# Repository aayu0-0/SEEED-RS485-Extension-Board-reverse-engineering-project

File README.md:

# Seeed Studio RS485 Extension Board — Reverse Engineering

A reverse-engineering and PCB recreation project of the **Seeed Studio RS485 Extension Board**.

The objective of this project is to understand the original board's electrical architecture, reproduce its schematic and PCB layout in KiCad, and generate a fabrication-ready design.

---

## 📌 Project Overview

This project involves analyzing the original Seeed Studio RS485 Extension Board and recreating its:

- Electrical schematic
- Power supply architecture
- RS485 communication interface
- Protection circuitry
- PCB layout
- Component footprints
- Manufacturing files

The recreated design is developed entirely in **KiCad**.

---

## 🎯 Objectives

- Reverse engineer the original RS485 extension board
- Understand the power and communication architecture
- Recreate the schematic in KiCad
- Select appropriate components and footprints
- Recreate the PCB layout
- Verify electrical connections and design rules
- Generate Gerber and drill files for PCB fabrication

---

## 🔧 Hardware

### Main Interfaces

- RS485 communication interface
- External power input
- Microcontroller/interface connection
- Protection circuitry

### Design Considerations

The design includes consideration for:

- RS485 differential signalling
- 120 Ω termination
- Fail-safe biasing
- Power regulation
- Reverse-polarity / transient protection
- Proper PCB grounding
- Controlled differential routing

---

## 🖥️ Software & Tools

| Tool | Purpose |
|------|---------|
| **KiCad** | Schematic and PCB design |
| **Git** | Version control |
| **GitHub** | Project hosting |
| **Datasheets** | Component verification |

---

## 📁 Repository Structure

```text
.
├── Home_Automation_v1.kicad_pro
├── Home_Automation_v1.kicad_sch
├── Home_Automation_v1.kicad_pcb
│
├── Home_Automation_v1.pretty/
│   └── Custom footprints
│
├── Final_Files/
│   ├── Gerber files
│   ├── Drill files
│   └── Gerber job file
│
└── README.md

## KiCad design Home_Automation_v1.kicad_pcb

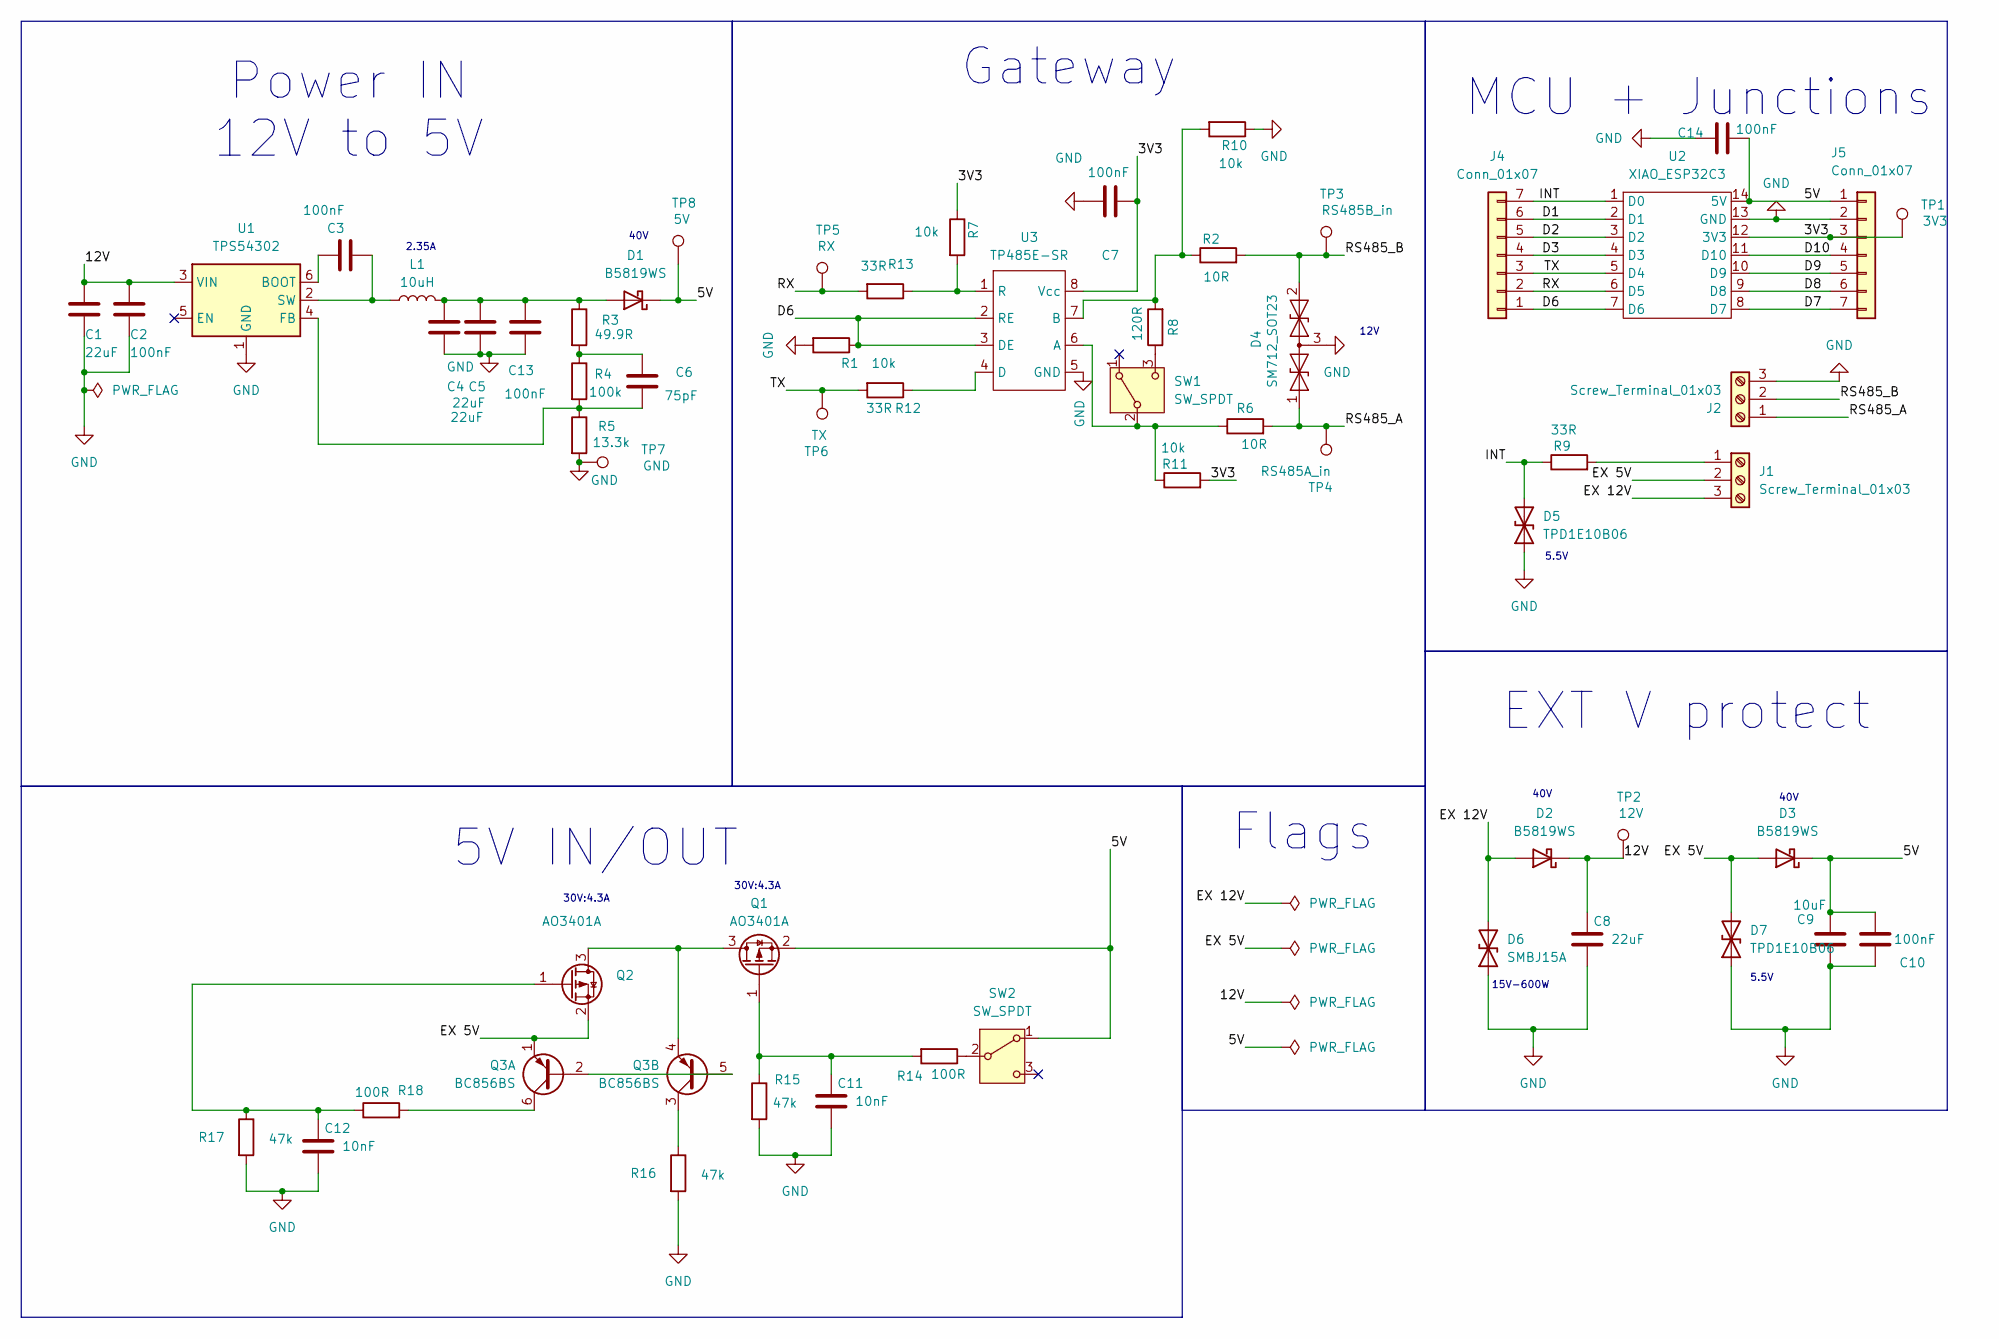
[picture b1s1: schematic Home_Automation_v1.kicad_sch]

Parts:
C1, C4, C5, C8: 22uF; C_0805_2012Metric
C2, C3, C7, C10, C13, C14: 100nF; C_0603_1608Metric
C6: 75pF; C_0603_1608Metric
C9: 10uF; C_0603_1608Metric
C11, C12: 10nF; C_0603_1608Metric
D1, D2, D3: B5819WS; D_SOD-323
D4: SM712_SOT23; SOT-23
D5, D7: TPD1E10B06; Texas_DPY0002A_0.6x1mm_P0.65mm
D6: SMBJ15A; D_SMB
J1, J2: Screw_Terminal_01x03; TerminalBlock_bornier-3_P5.08mm
J4, J5: Conn_01x07; PinHeader_1x07_P2.54mm_Vertical
L1: 10uH; L_Vishay_IHLP-2525
Q1, Q2: AO3401A; SOT-23
Q3: BC856BS; SOT-363_SC-70-6
R1, R7, R10, R11: 10k; R_0603_1608Metric
R2, R6: 10R; R_0603_1608Metric
R3: 49.9R; R_0603_1608Metric
R4: 100k; R_0603_1608Metric
R5: 13.3k; R_0603_1608Metric
R8: 120R; R_0603_1608Metric
R9, R12, R13: 33R; R_0603_1608Metric
R14, R18: 100R; R_0603_1608Metric
R15, R16, R17: 47k; R_0603_1608Metric
SW1, SW2: SW_SPDT; SW-SMD_G-SWITCH_MK-12C02-G015
TP1: 3V3; TestPoint_Pad_D1.5mm
TP2: 12V; TestPoint_Pad_D1.5mm
TP3: RS485B_in; TestPoint_Pad_D1.5mm
TP4: RS485A_in; TestPoint_Pad_D1.5mm
TP5: RX; TestPoint_Pad_D1.5mm
TP6: TX; TestPoint_Pad_D1.5mm
TP7: GND; TestPoint_Pad_D1.5mm
TP8: 5V; TestPoint_Pad_D1.5mm
U1: TPS54302; SOT-23-6
U2: XIAO_ESP32C3; MCU_Seeed_ESP32C3
U3: TP485E-SR; SOIC-8_3.9x4.9mm_P1.27mm

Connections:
/3V3: C7.1, J5.3, R7.1, R11.2, TP1.1 (1_1), U2.12 (3V3), U3.8 (Vcc)
/5V: C9.1, C10.1, C14.2, D1.1 (K), D3.1 (K), J5.1, Q1.2 (S), SW2.1 (A), TP8.1 (1_1), U2.14 (5V)
/12V: C1.1, C2.1, C8.1, D2.1 (K), TP2.1 (1_1), U1.3 (VIN)
/D1: J4.6, U2.2 (D1)
/D2: J4.5, U2.3 (D2)
/D3: J4.4, U2.4 (D3)
/D6: J4.1, R1.1, U2.7 (D6), U3.2 (RE), U3.3 (DE)
/D7: J5.7, U2.8 (D7)
/D8: J5.6, U2.9 (D8)
/D9: J5.5, U2.10 (D9)
/D10: J5.4, U2.11 (D10)
/EX 5V: D3.2 (A), D7.2 (A2), J1.2, Q2.2 (S), Q3.1 (E1)
/EX 12V: D2.2 (A), D6.2 (A2), J1.3
/INT: D5.2 (A2), J4.7, R9.1, U2.1 (D0)
/RS485_A: D4.1 (A1), J2.1, R6.2, TP4.1 (1_1)
/RS485_B: D4.2 (A2), J2.2, R2.2, TP3.1 (1_1)
/RX: J4.2, R13.2, TP5.1 (1_1), U2.6 (D5)
/TX: J4.3, R12.2, TP6.1 (1_1), U2.5 (D4)
GND: C1.2, C2.2, C4.2, C5.2, C7.2, C8.2, C9.2, C10.2, C11.2, C12.2, C13.2, C14.1, D4.3 (common), D5.1 (A1), D6.1 (A1), D7.1 (A1), J2.3, J5.2, R1.2, R5.2, R10.1, R15.2, R16.2, R17.2, TP7.1 (1_1), U1.1 (GND), U2.13 (GND), U3.5 (GND)
unnamed: C6.1, R3.2, R4.1
unnamed: C4.1, C5.1, C13.1, D1.2 (A), L1.2, R3.1
unnamed: J1.1, R9.2
unnamed: Q1.3 (D), Q2.3 (D), Q3.4 (E2)
unnamed: C11.1, Q1.1 (G), R14.2, R15.1
unnamed: C12.1, Q2.1 (G), R17.1, R18.1
unnamed: Q3.2 (B1), Q3.5 (B2)
unnamed: Q3.6 (C1), R18.2
unnamed: Q3.3 (C2), R16.1
unnamed: R6.1, R11.1, SW1.2 (B), U3.6 (A)
unnamed: R8.1, SW1.3 (C)
unnamed: R14.1, SW2.2 (B)
unnamed: C3.1, U1.6 (BOOT)
unnamed: C6.2, R4.2, R5.1, U1.4 (FB)
unnamed: C3.2, L1.1, U1.2 (SW)
unnamed: R2.1, R8.2, R10.2, U3.7 (B)
unnamed: R12.1, U3.4 (D)
unnamed: R7.2, R13.1, U3.1 (R)

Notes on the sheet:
Gateway
2.35A
40V
30V:4.3A
MCU + Junctions
40V
5V IN/OUT
5.5V
15V-600W
Flags
5.5V
12V
EXT V protect
Power IN 12V to 5V

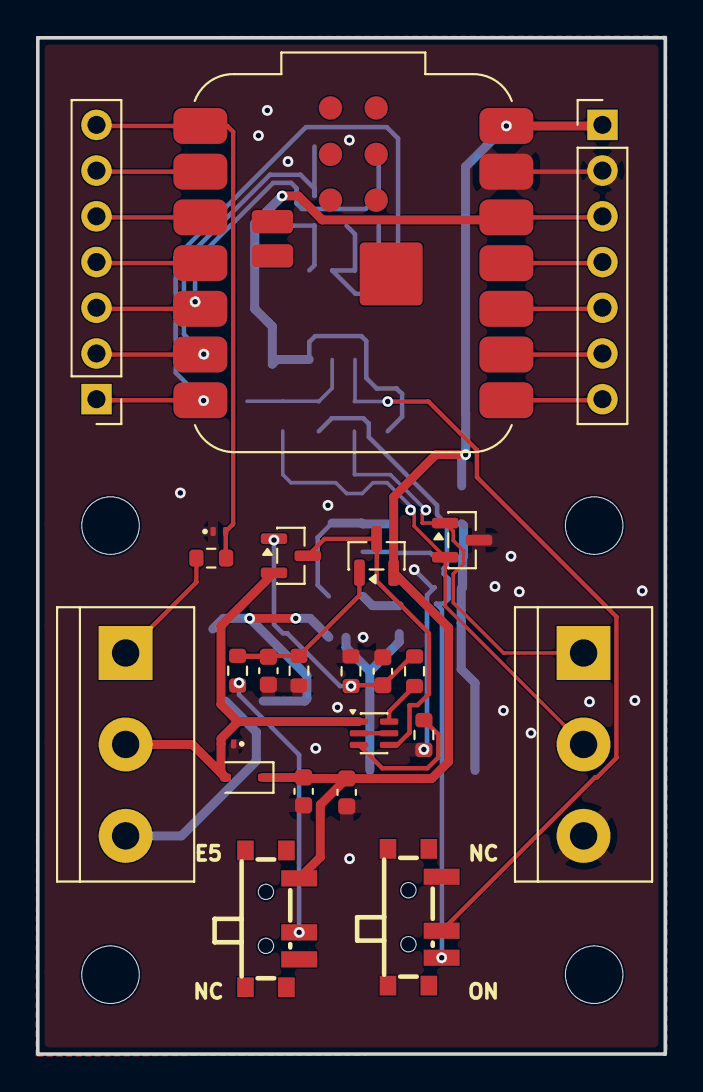
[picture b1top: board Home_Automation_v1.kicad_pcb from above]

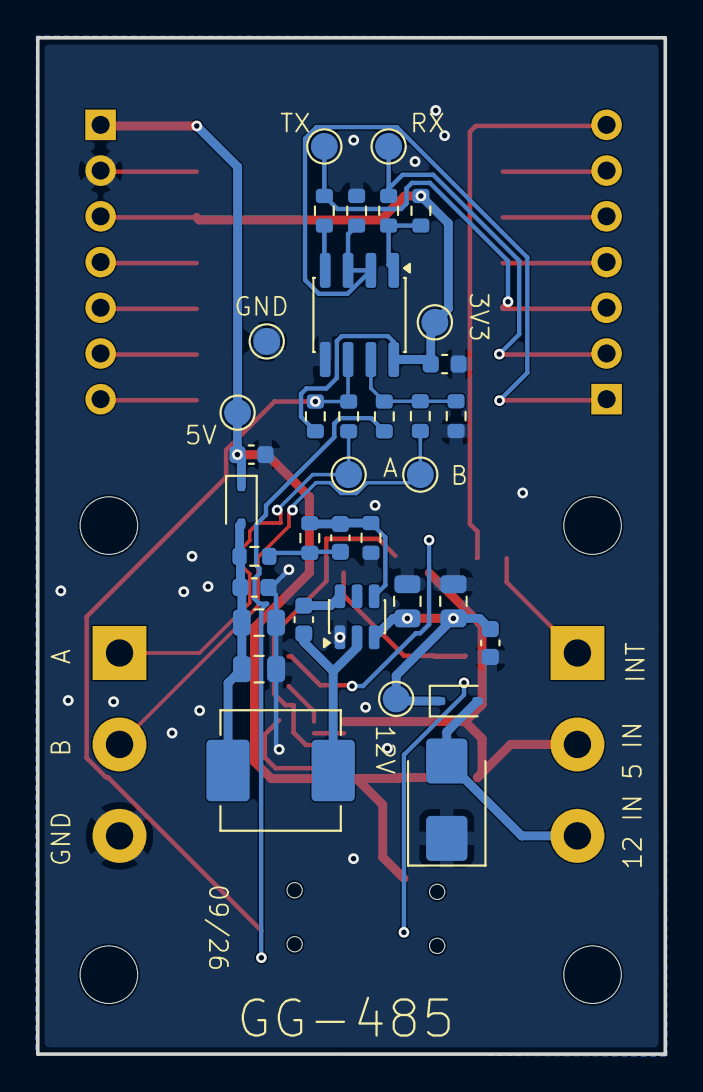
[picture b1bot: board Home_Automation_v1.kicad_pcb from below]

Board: 2 copper layers, 34.9 x 56.5 mm, 60 parts (36 on the bottom side), 37 nets.
